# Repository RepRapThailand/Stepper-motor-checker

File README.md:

# Stepper-motor-checker
[https://tinkersprojects.com/](https://tinkersprojects.com/)

This device replaces or attach to current stepper motor controllers for 3D printers and CNC machines to error correct the steps. Using a sensor that can sense rotational location, the corrector can change the steps to correct the errors. This technology exists already but gets controlled by the main controller. All cheaper machines will not have in the built in to it but this device will increase the accuracy in these machines.

The PCB can be purchased from https://tinkersprojects.com/product/stepper-motor-monitor/

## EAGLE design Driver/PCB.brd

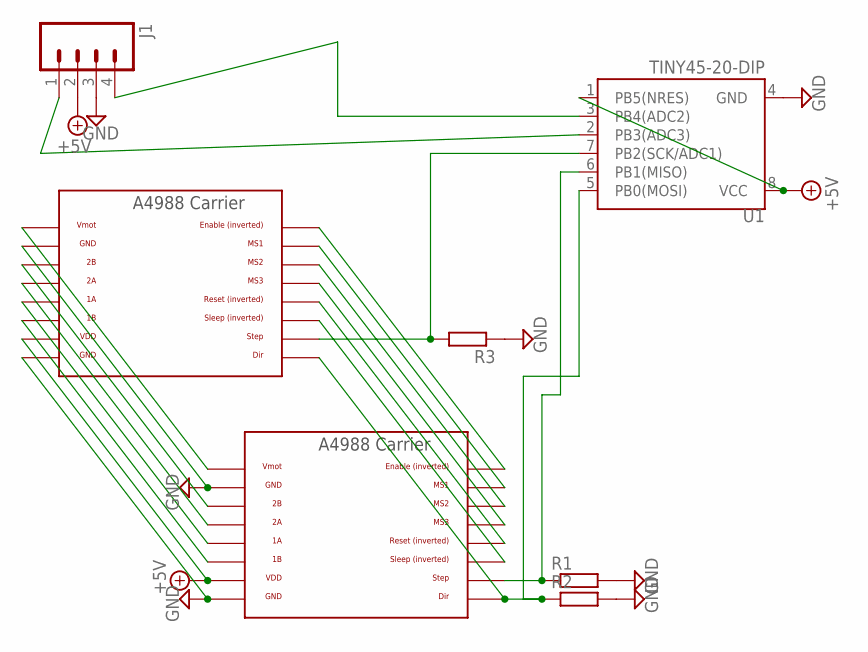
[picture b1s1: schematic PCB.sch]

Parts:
J1: M04JST-PTH-VERT; JST-4-PTH-VERT
R1, R2, R3: R-EU_R0805; R0805
U1: TINY45-20-DIP; DIP08
U$1, U$2: A4988BREAKOUT

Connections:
+5V: J1.2, U1.1 (PB5(NRES)), U1.8 (VCC), U$1.VDD, U$2.VDD
GND: J1.3, R1.2, R2.2, R3.1, U1.4 (GND), U$1.GND, U$1.GND@0 (GND), U$2.GND, U$2.GND@0 (GND)
unnamed: U$1.EN, U$2.EN
unnamed: U$1.MS1, U$2.MS1
unnamed: U$1.MS2, U$2.MS2
unnamed: U$1.MS3, U$2.MS3
unnamed: U$1.RST, U$2.RST
unnamed: U$1.SLP (SLEEP), U$2.SLP (SLEEP)
unnamed: R1.1, U1.6 (PB1(MISO)), U$2.STEP
unnamed: R2.1, U1.5 (PB0(MOSI)), U$1.DIR, U$2.DIR
unnamed: R3.2, U1.7 (PB2(SCK/ADC1)), U$1.STEP
unnamed: J1.4, U1.3 (PB4(ADC2))
unnamed: U$1.1B, U$2.1B
unnamed: U$1.1A, U$2.1A
unnamed: U$1.2A, U$2.2A
unnamed: U$1.2B, U$2.2B
unnamed: J1.1, U1.2 (PB3(ADC3))
unnamed: U$1.VMOT, U$2.VMOT

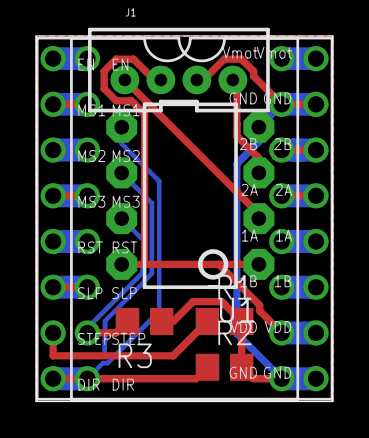
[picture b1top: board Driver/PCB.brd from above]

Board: 2 copper layers, 16.5 x 20.3 mm, 7 parts (0 on the bottom side), 18 nets.

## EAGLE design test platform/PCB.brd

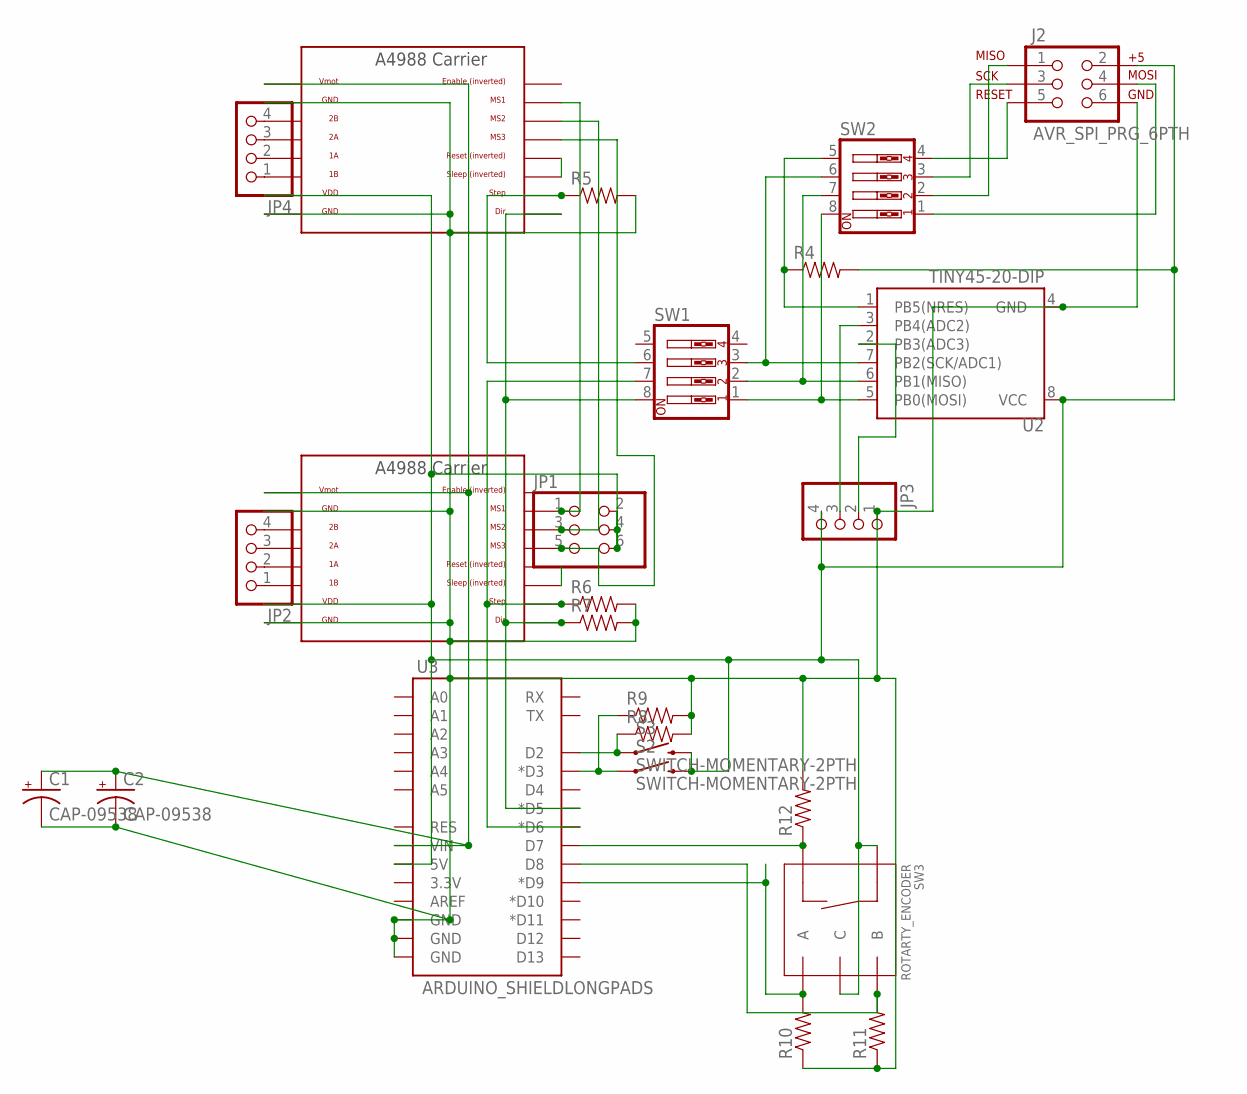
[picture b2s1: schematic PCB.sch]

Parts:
C1, C2: CAP-09538; CPOL-RADIAL-1000UF-25V
J2: AVR_SPI_PRG_6PTH; 2X3
JP1: PINHD-2X3; 2X03
JP2, JP3, JP4: PINHD-1X4; 1X04
R4, R5, R6, R7, R8, R9, R10, R11, R12: RESISTOR1206; 1206
S2, S3: SWITCH-MOMENTARY-2PTH; TACTILE-PTH
SW1, SW2: SW_DIP-4; EDG-04
SW3: ROTARTY_ENCODER; ROTARY_ENC_PLAIN
U2: TINY45-20-DIP; DIP08
U3: ARDUINO_SHIELDLONGPADS; DUEMILANOVE_SHIELD_LONGPADS
U$3, U$4: A4988BREAKOUT

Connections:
unnamed: JP1.1, U$3.MS1, U$4.MS1
unnamed: JP1.3, U$3.MS2, U$4.MS2
unnamed: JP1.5, U$3.MS3, U$4.MS3
unnamed: JP2.1, U$3.1B
unnamed: JP2.2, U$3.1A
unnamed: JP2.3, U$3.2A
unnamed: JP2.4, U$3.2B
unnamed: R9.1, S2.1, U3.D3 (*D3)
unnamed: U$3.RST, U$3.SLP (SLEEP)
unnamed: R5.1, SW1.6, U$4.STEP
unnamed: R6.1, SW1.7, U3.D6 (*D6), U$3.STEP
unnamed: R7.1, SW1.8, U3.D5 (*D5), U$3.DIR, U$4.DIR
unnamed: R8.1, S3.1, U3.D2
unnamed: JP3.3, U2.3 (PB4(ADC2))
unnamed: JP3.2, U2.2 (PB3(ADC3))
unnamed: JP4.1, U$4.1B
unnamed: JP4.2, U$4.1A
unnamed: JP4.3, U$4.2A
unnamed: JP4.4, U$4.2B
unnamed: R10.2, SW3.A, U3.D9 (*D9)
unnamed: U$4.RST, U$4.SLP (SLEEP)
unnamed: C1.+, C2.+, U3.VIN, U$3.VMOT, U$4.VMOT
unnamed: J2.2, JP1.2, JP1.4, JP1.6, JP3.4, R4.2, S2.3 (2), S3.3 (2), SW3.C, SW3.SW+, U2.8 (VCC), U3.5V, U$3.VDD, U$4.VDD
unnamed: R11.2, SW3.B, U3.D8
unnamed: R12.1, SW3.SW-, U3.D7
unnamed: J2.4, SW2.1
unnamed: J2.1, SW2.2
unnamed: J2.3, SW2.3
unnamed: J2.5, SW2.4
unnamed: R4.1, SW2.5, U2.1 (PB5(NRES))
unnamed: SW1.3, SW2.6, U2.7 (PB2(SCK/ADC1))
unnamed: SW1.2, SW2.7, U2.6 (PB1(MISO))
unnamed: SW1.1, SW2.8, U2.5 (PB0(MOSI))
unnamed: C1.-, C2.-, J2.6, JP3.1, R5.2, R6.2, R7.2, R8.2, R9.2, R10.1, R11.1, R12.2, U2.4 (GND), U3.GND@0 (GND), U3.GND@1 (GND), U3.GND@2 (GND), U$3.GND, U$3.GND@0 (GND), U$4.GND, U$4.GND@0 (GND)

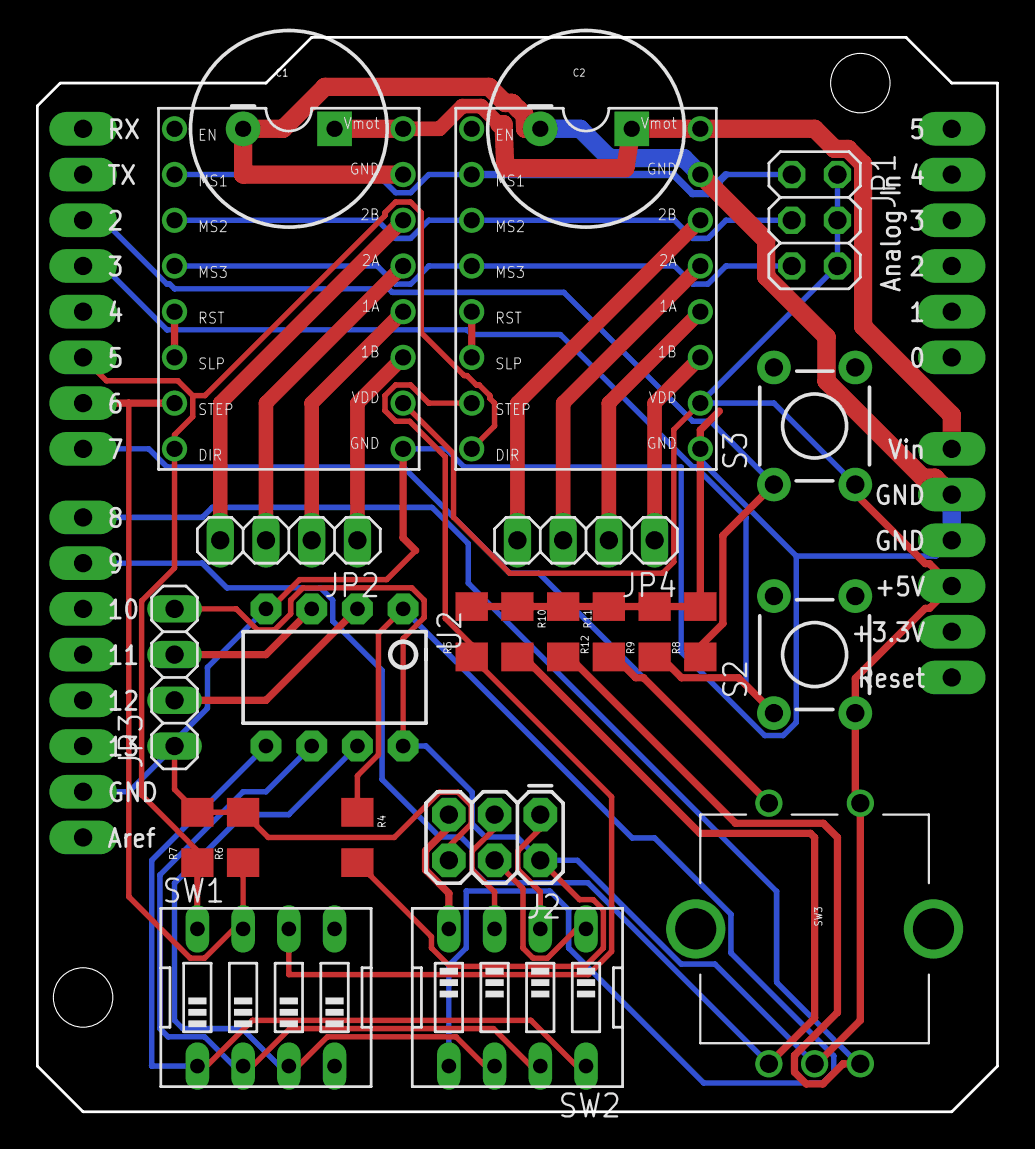
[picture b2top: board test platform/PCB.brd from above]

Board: 2 copper layers, 53.3 x 59.7 mm, 25 parts (0 on the bottom side), 34 nets.

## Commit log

2018-04-12 Add files via upload
    file upload

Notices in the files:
parts and their libraries:
SparkFun-DigitalIC: Licensing: Creative Commons ShareAlike 4.0 International - https://creativecommons.org/licenses/by-sa/4.0
